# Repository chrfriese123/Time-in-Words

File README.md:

# Time expressed by words

## Introduction

The concept of presenting the current time by individual words is not new and demonstrated quite often e.g. on Youtube. Out of curiousity this private project was started without considering too much input from other sources. The goal was to prepare one working demonstrator. 

## Basic setup

The principle setup consist of a front plate with cut-outs for the indiviual letters, an illumnination electronic behind each letter and a control circuit to control the individual LEDs.

### Front plate
For the front plate a suitbale svg template was created with Inkscape. All together over 100 letters are required. The file was then transferred with laser cutting into a steel plate. To have a stable, non bending plate, 2mm steel was choosen.

*Lessons learned: this is (too) heavy, thinner would be acceptable.*

### Electronics
To generate a uniform illumniation behind each letter, two RGBW LEDs (SK6812) were considered for each letter. This sums up to a total of over 200 LEDs that needed to be driven and powered in a row. They are mounted on individual small PCBs as this approach seemed more cost efficient than having a huge PCB behind the entire front plate. 

*Lessons learned: lot of soldering between the PCBs needed.*

### Control units
An ESP32 based setup was choosen to drive the LEDs. A simple look-up table is used to translate the current time into a definition of which LED to switch on/off. The time is retrieved by NTP which turned out to be not reliable enough. Adding a RTC to the setup solved the challenge. The power is supplied by a USB-C connection providing sufficient power. To control the behavior (color & intensity) of the clock, a simple async server was setup on the ESP. 

*Lessons learned: do not rely on Wifi, use RTC as backup.*

### Assembly
For aligning the PCBs to the letters a 3D printed frame was used. This frame also prevents cross-talk of the illumnation between the different elements. To hide the LEDs from the frontside, the frame was partially filled with epoxy. White pigments were added to the epoxy. Unfortunately this lead to a color shift of the LEDs and less defined appearance. To hide all the installation, hot glue and flying wires a wooden backplate was attached to the setup.

*Lessons learned: "white" epoxy screws up color fidelity.*

## Conclusion
The demonstrator works and looks nice. I used and combined a couple of new technologies (for myself) and learned a lot for future projects. After considering all the effort (material, hours), it seems more reasonable, why a commercial product is expensive.

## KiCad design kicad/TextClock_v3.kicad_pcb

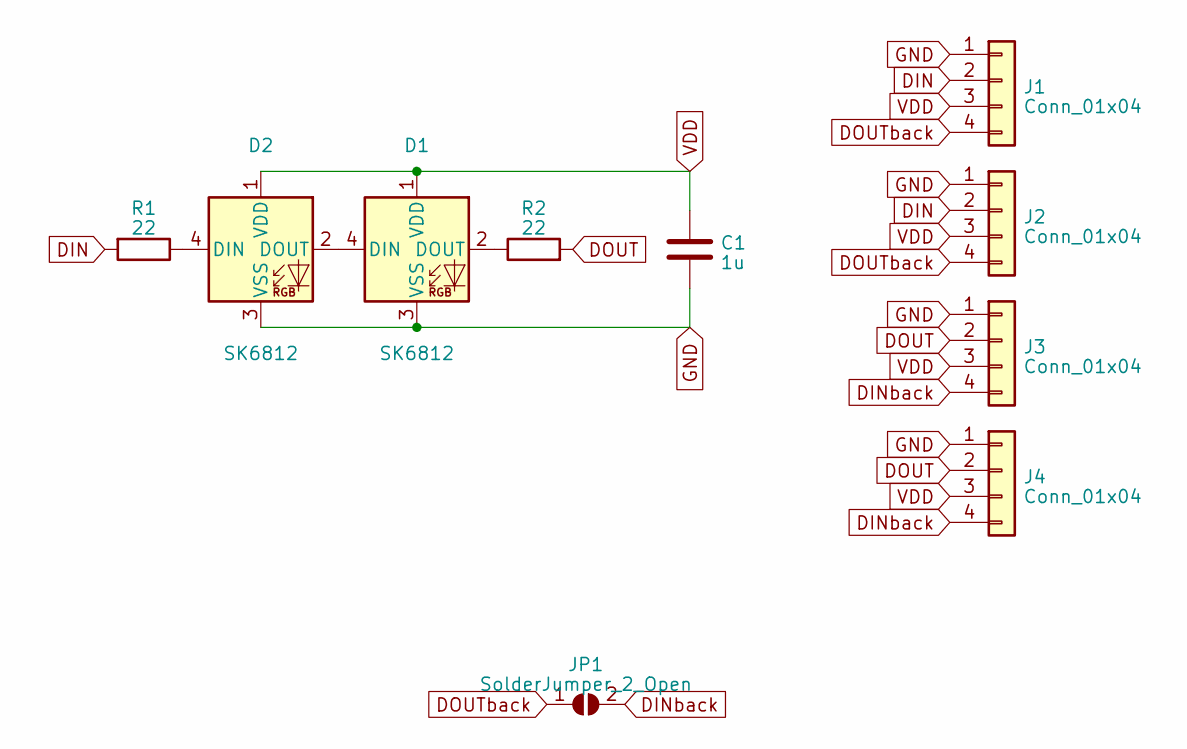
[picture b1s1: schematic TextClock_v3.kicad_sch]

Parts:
C1: 1u; C_0805_2012Metric_Pad1.18x1.45mm_HandSolder
D1, D2: SK6812; LED_WS2812B_PLCC4_5.0x5.0mm_P3.2mm
J1, J2, J3, J4: Conn_01x04; PinHeader_1x04_P2.54mm_Vertical
JP1: SolderJumper_2_Open; SolderJumper-2_P1.3mm_Open_RoundedPad1.0x1.5mm
R1, R2: 22; R_0805_2012Metric_Pad1.20x1.40mm_HandSolder

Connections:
DIN: J1.2, J2.2, R1.2
DINback: J3.4, J4.4, JP1.2 (B)
DOUT: J3.2, J4.2, R2.2
DOUTback: J1.4, J2.4, JP1.1 (A)
GND: C1.2, D1.3 (VSS), D2.3 (VSS), J1.1, J2.1, J3.1, J4.1
unnamed: D1.4 (DIN), D2.2 (DOUT)
unnamed: D1.2 (DOUT), R2.1
unnamed: D2.4 (DIN), R1.1
VDD: C1.1, D1.1 (VDD), D2.1 (VDD), J1.3, J2.3, J3.3, J4.3

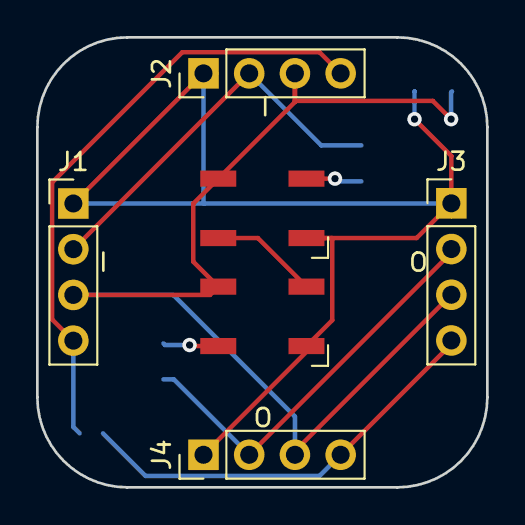
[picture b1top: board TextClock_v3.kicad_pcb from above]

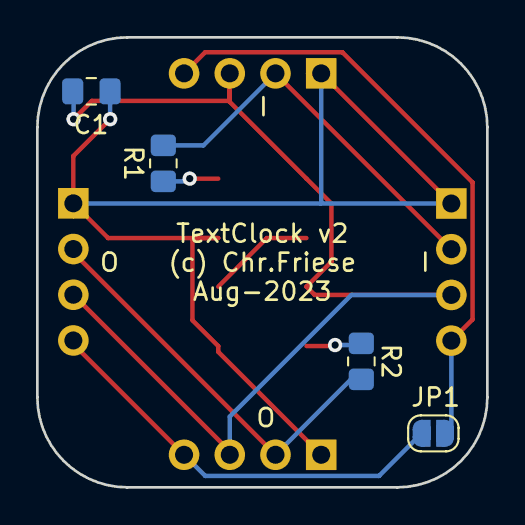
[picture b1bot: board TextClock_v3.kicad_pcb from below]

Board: 2 copper layers, 25.0 x 25.0 mm, 10 parts (4 on the bottom side), 9 nets.
